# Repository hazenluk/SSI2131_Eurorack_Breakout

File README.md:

# SSI2131_Eurorack_Breakout
Single PCB Eurorack Module for SSI2131. Potentiometers and jacks are mounted to the backside of the PCB, which also serves as the front of the module.

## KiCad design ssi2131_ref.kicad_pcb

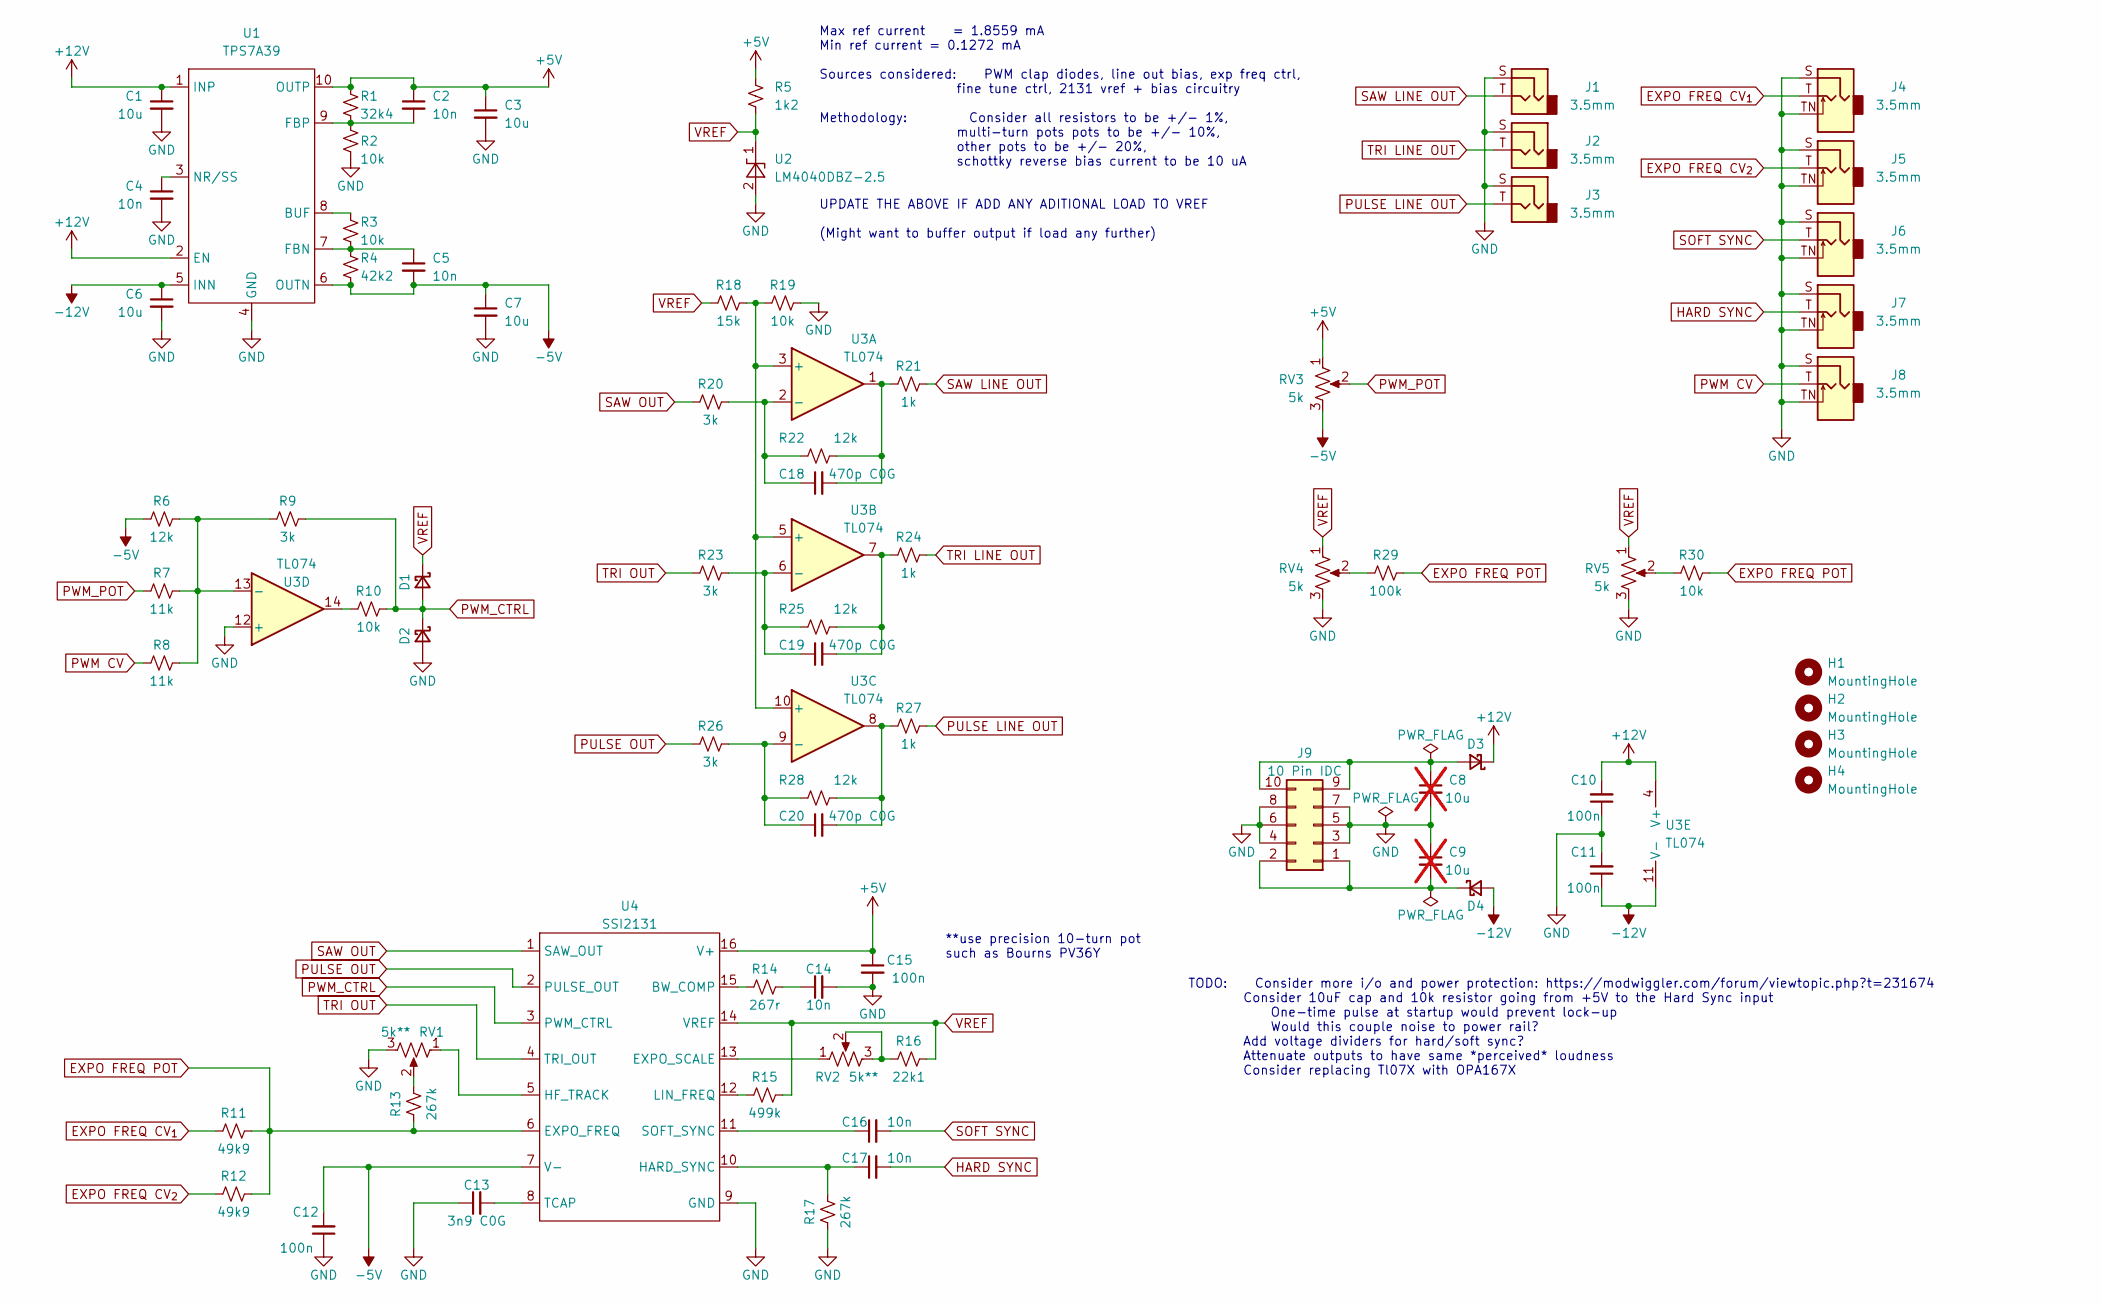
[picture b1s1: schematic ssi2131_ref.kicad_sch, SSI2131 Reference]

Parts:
C1, C3, C6, C7: 10u; C_0603_1608Metric
C2, C4, C5, C14, C16, C17: 10n; C_0402_1005Metric
C8, C9: 10u; C_0603_1608Metric; not fitted
C10, C11, C12, C15: 100n; C_0402_1005Metric
C13: 3n9 C0G; C_0603_1608Metric
C18, C19, C20: 470p C0G; C_0402_1005Metric
D1, D2, D3, D4: D_Schottky_Small; D_SOD-323
H1, H2, H3, H4: MountingHole; MountingHole_3.2mm_M3
J1, J2, J3: 3.5mm; PJ-301BM
J4, J5, J6, J7, J8: 3.5mm; PJ-301BM_disconnect
J9: 10 Pin IDC; IDC-Header_2x05_P2.54mm_Vertical_SMD
R1: 32k4; R_0402_1005Metric
R2, R3, R10, R19, R30: 10k; R_0402_1005Metric
R4: 42k2; R_0402_1005Metric
R5: 1k2; R_0402_1005Metric
R6, R22, R25, R28: 12k; R_0402_1005Metric
R7, R8: 11k; R_0603_1608Metric
R9, R20, R23, R26: 3k; R_0603_1608Metric
R11, R12: 49k9; R_0402_1005Metric
R13, R17: 267k; R_0402_1005Metric
R14: 267r; R_0402_1005Metric
R15: 499k; R_0402_1005Metric
R16: 22k1; R_0402_1005Metric
R18: 15k; R_0402_1005Metric
R21, R24, R27: 1k; R_0402_1005Metric
R29: 100k; R_0402_1005Metric
RV1, RV2: 5k**; Potentiometer_Bourns_3224W_Vertical
RV3, RV4, RV5: 5k; Potentiometer_Alpha_RD901F-40-00D_Single_Vertical_Bodge
U1: TPS7A39; Texas_DSC0010J
U2: LM4040DBZ-2.5; SOT-23
U3: TL074; TSSOP-14_4.4x5mm_P0.65mm
U4: SSI2131; SOP-16_4.55x10.3mm_P1.27mm

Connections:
+5V: C2.1, C3.1, C15.1, R1.1, R5.1, RV3.1, U1.10 (OUTP), U4.16 (V+)
+12V: C1.1, C10.2, D3.1 (K), U1.1 (INP), U1.2 (EN), U3.4 (V+)
-5V: C5.2, C7.1, C12.2, R4.2, R6.1, RV3.3, U1.6 (OUTN), U4.7 (V-)
-12V: C6.1, C11.1, D4.2 (A), U1.5 (INN), U3.11 (V-)
EXPO FREQ CV_{1}: J4.T, R11.1
EXPO FREQ CV_{2}: J5.T, R12.1
EXPO FREQ POT: R11.2, R12.2, R13.1, R29.2, R30.2, U4.6 (EXPO_FREQ)
GND: C1.2, C3.2, C4.2, C6.2, C7.2, C8.2, C9.1, C10.1, C11.2, C12.1, C13.1, C14.2, C15.2, D2.2 (A), J1.S, J2.S, J3.S, J4.S, J4.TN, J5.S, J5.TN, J6.S, J6.TN, J7.S, J7.TN, J8.S, J8.TN, J9.3, J9.4, J9.5, J9.6, J9.7, J9.8, R2.2, R17.1, R19.2, RV1.3, RV4.3, RV5.3, U1.4 (GND), U1.11 (GND), U2.2 (A), U3.12 (+), U4.9 (GND)
HARD SYNC: C17.2, J7.T
unnamed: C14.1, R14.2
unnamed: C18.2, R21.1, R22.2, U3.1
unnamed: C19.2, R24.1, R25.2, U3.7
unnamed: C20.2, R27.1, R28.2, U3.8
unnamed: C8.1, D3.2 (A), J9.9, J9.10
unnamed: C9.2, D4.1 (K), J9.1, J9.2
unnamed: R10.1, U3.14
unnamed: R13.2, RV1.2
unnamed: R16.1, RV2.2, RV2.3
unnamed: R29.1, RV4.2
unnamed: R30.1, RV5.2
unnamed: R3.1, U1.8 (BUF)
unnamed: C5.1, R3.2, R4.1, U1.7 (FBN)
unnamed: C2.2, R1.2, R2.1, U1.9 (FBP)
unnamed: C4.1, U1.3 (NR/SS)
unnamed: R18.2, R19.1, U3.3 (+), U3.5 (+), U3.10 (+)
unnamed: C18.1, R20.2, R22.1, U3.2 (-)
unnamed: C19.1, R23.2, R25.1, U3.6 (-)
unnamed: C20.1, R26.2, R28.1, U3.9 (-)
unnamed: R6.2, R7.2, R8.2, R9.1, U3.13 (-)
unnamed: R14.1, U4.15 (BW_COMP)
unnamed: RV2.1, U4.13 (EXPO_SCALE)
unnamed: C17.1, R17.2, U4.10 (HARD_SYNC)
unnamed: RV1.1, U4.5 (HF_TRACK)
unnamed: R15.1, U4.12 (LIN_FREQ)
unnamed: C16.1, U4.11 (SOFT_SYNC)
unnamed: C13.2, U4.8 (TCAP)
PULSE LINE OUT: J3.T, R27.2
PULSE OUT: R26.1, U4.2 (PULSE_OUT)
PWM CV: J8.T, R8.1
PWM_CTRL: D1.2 (A), D2.1 (K), R9.2, R10.2, U4.3 (PWM_CTRL)
PWM_POT: R7.1, RV3.2
SAW LINE OUT: J1.T, R21.2
SAW OUT: R20.1, U4.1 (SAW_OUT)
SOFT SYNC: C16.2, J6.T
TRI LINE OUT: J2.T, R24.2
TRI OUT: R23.1, U4.4 (TRI_OUT)
VREF: D1.1 (K), R5.2, R15.2, R16.2, R18.1, RV4.1, RV5.1, U2.1 (K), U4.14 (VREF)

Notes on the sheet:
**use precision 10-turn pot such as Bourns PV36Y
UPDATE THE ABOVE IF ADD ANY ADITIONAL LOAD TO VREF (Might want to buffer output if load any further)
Max ref current = 1.8559 mA Min ref current = 0.1272 mA Sources considered: PWM clap diodes, line out bias, exp freq ctrl, fine tune ctrl, 2131 vref + bias circuitry Methodology: Consider all resistors to be +/- 1%, multi-turn pots pots to be +/- 10%, other pots to be +/- 20%, schottky reverse bias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
TODO: Consider more i/o and power protection: https://modwiggler.com/forum/viewtopic.php?t=231674 Consider 10uF cap and 10k resistor going from +5V to the Hard Sync input One-time pulse at startup would prevent lock-up Would this couple noise to power rail? Add voltage dividers for hard/soft sync? 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

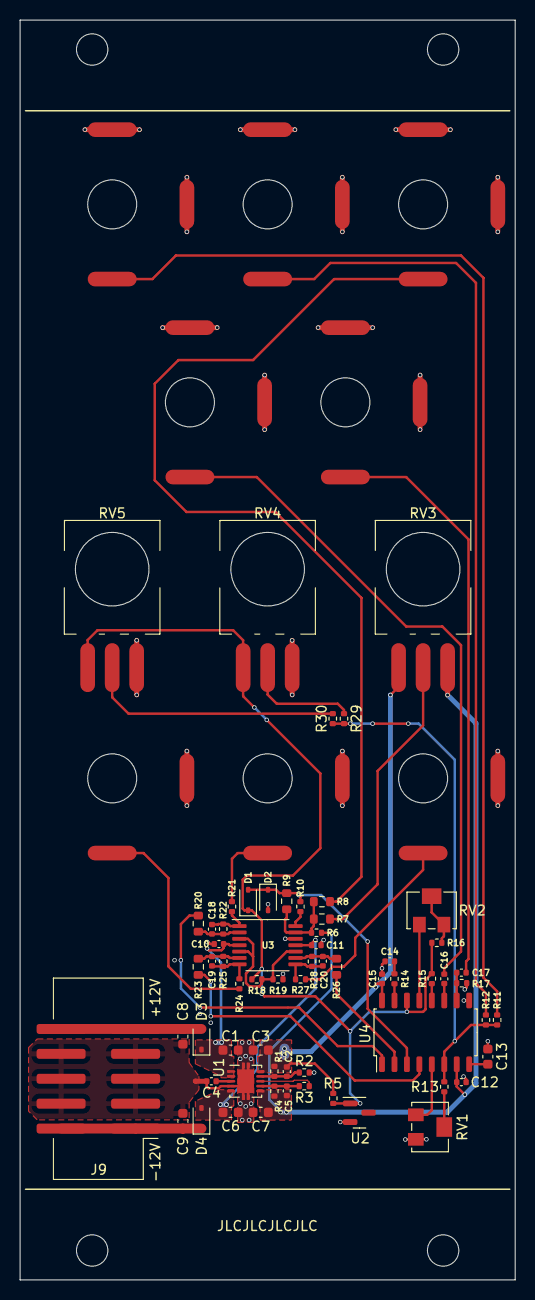
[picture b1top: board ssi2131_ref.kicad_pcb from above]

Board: 4 copper layers, 50.5 x 128.5 mm, 76 parts (0 on the bottom side), 47 nets.

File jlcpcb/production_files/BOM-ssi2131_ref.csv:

Comment,Designator,Footprint,LCSC
1k,"R21,R24,R27",R_0402_1005Metric,C11702
LM4040DBZ-2.5,U2,SOT-23,C131939
499k,R15,R_0402_1005Metric,C137971
10n,"C14,C16,C17,C2,C4,C5",C_0402_1005Metric,C15195
100n,"C10,C11,C12,C15",C_0402_1005Metric,C1525
D_Schottky_Small,"D1,D2,D3,D4",D_SOD-323,C191023
267r,R14,R_0402_1005Metric,C226381
32k4,R1,R_0402_1005Metric,C226993
100k,R29,R_0402_1005Metric,C25741
10k,"R10,R19,R30",R_0402_1005Metric,C25744
12k,"R22,R25,R28,R6",R_0402_1005Metric,C25752
15k,R18,R_0402_1005Metric,C25756
22k1,R16,R_0402_1005Metric,C25768
1k2,R5,R_0402_1005Metric,C25862
49k9,"R11,R12",R_0402_1005Metric,C25897
11k,"R7,R8",R_0603_1608Metric,C25950
TPS7A39,U1,Texas_DSC0010J,C2685819
10k,"R2,R3",R_0402_1005Metric,C2692697
267k,"R13,R17",R_0402_1005Metric,C270622
10 Pin IDC,J9,IDC-Header_2x05_P2.54mm_Vertical_SMD,C2843214
3n9 C0G,C13,C_0603_1608Metric,C415537
3k,"R20,R23,R26,R9",R_0603_1608Metric,C4211
470p C0G,"C18,C19,C20",C_0402_1005Metric,C76971
5k**,"RV1,RV2",Potentiometer_Bourns_3224W_Vertical,C81349
42k2,R4,R_0402_1005Metric,C852782
10u,"C1,C3,C6,C7,C8,C9",C_0603_1608Metric,C96446
TL074,U3,TSSOP-14_4.4x5mm_P0.65mm,C96507
3.5mm,J7,PJ-301BM_disconnect,
3.5mm,J6,PJ-301BM_disconnect,
SSI2131,U4,SOP-16_4.55x10.3mm_P1.27mm,
3.5mm,J2,PJ-301BM,
3.5mm,J1,PJ-301BM,
5k,RV5,Potentiometer_Alpha_RD901F-40-00D_Single_Vertical_Bodge,
5k,RV3,Potentiometer_Alpha_RD901F-40-00D_Single_Vertical_Bodge,
3.5mm,J3,PJ-301BM,
3.5mm,J5,PJ-301BM_disconnect,
3.5mm,J4,PJ-301BM_disconnect,
3.5mm,J8,PJ-301BM_disconnect,
5k,RV4,Potentiometer_Alpha_RD901F-40-00D_Single_Vertical_Bodge,
MountingHole,H4,MountingHole_3.2mm_M3,
MountingHole,H3,MountingHole_3.2mm_M3,
MountingHole,H2,MountingHole_3.2mm_M3,
MountingHole,H1,MountingHole_3.2mm_M3,

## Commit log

2023-09-28 Upload to github
2023-09-28 Clened repo; stopped tracking backup files
2023-09-28 Tracking PDFs with LFS
2023-09-28 Added board images
